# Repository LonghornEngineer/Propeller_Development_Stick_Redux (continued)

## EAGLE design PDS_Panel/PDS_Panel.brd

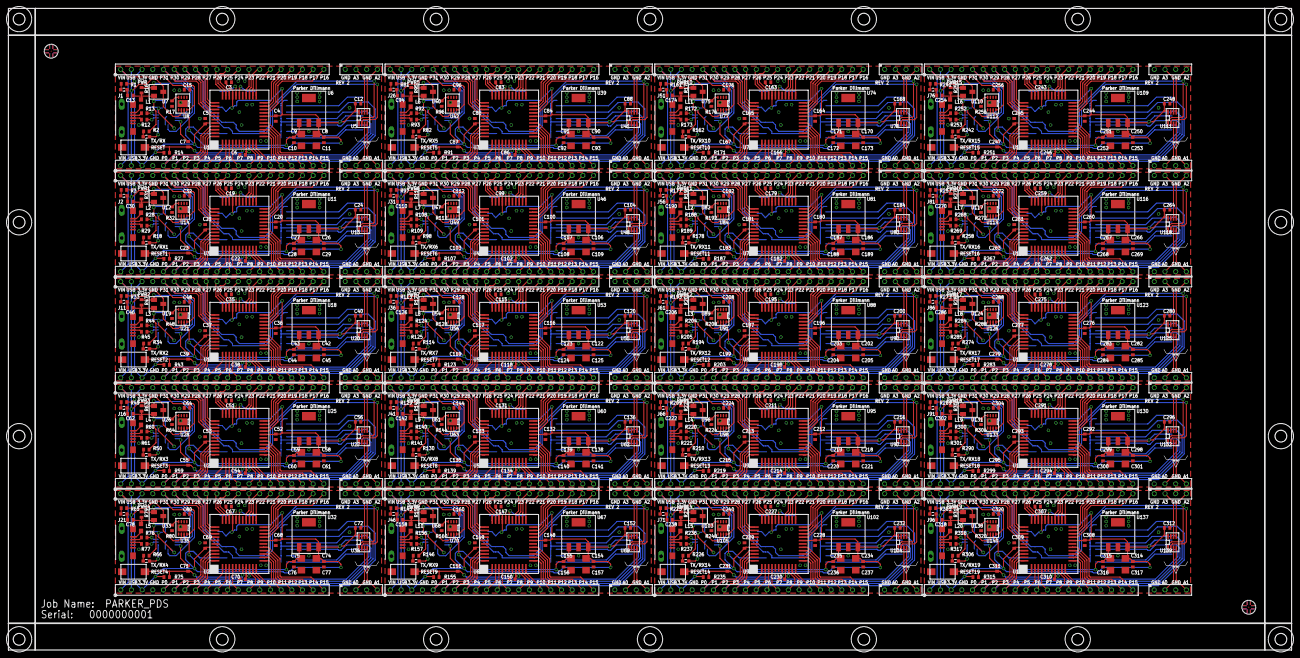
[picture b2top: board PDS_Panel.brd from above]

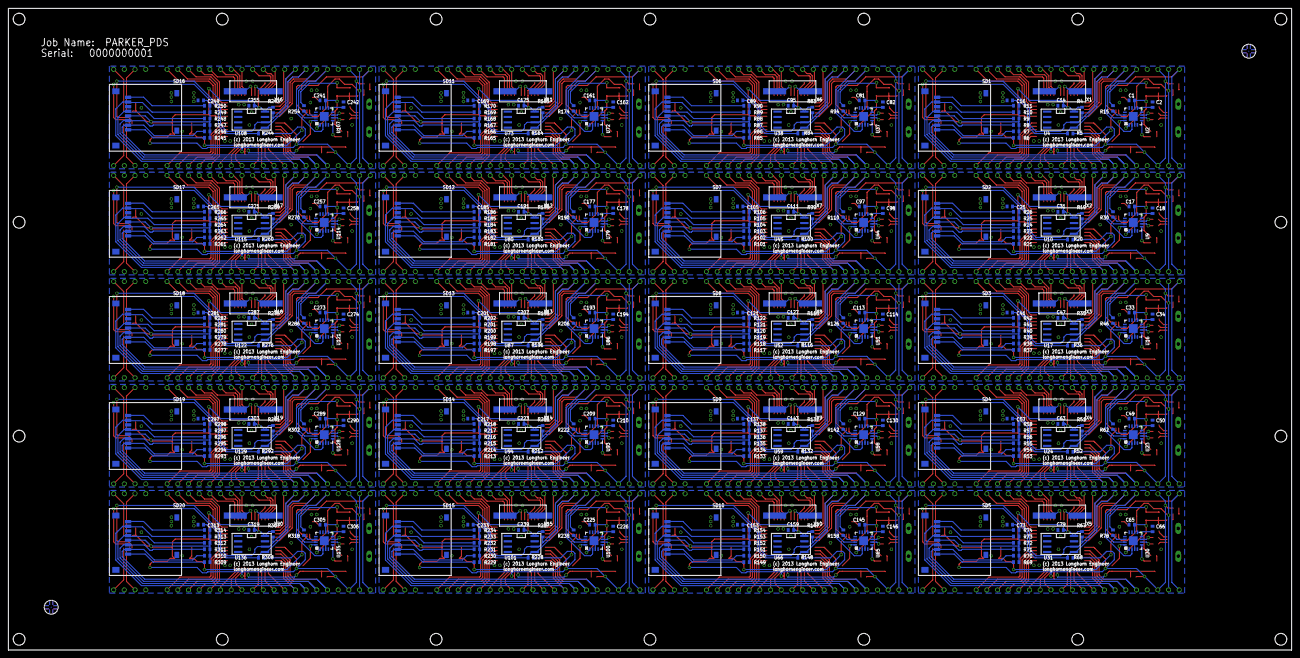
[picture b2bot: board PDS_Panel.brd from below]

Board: 2 copper layers, 304.8 x 152.4 mm, 1062 parts (362 on the bottom side), 1200 nets.

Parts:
C1, C2, C3, C4, C5, C6, C7, C10, C11, C12, C13, C14, C15, C16, C17, C18, C19, C20, C21, C22, C23, C24, C25, C28, C29, C30, C31, C32, C33, C34, C35, C36, C37, C38, C39, C40, C41, C44, C45, C46, C47, C48, C49, C50, C51, C52, C53, C54, C55, C56, C57, C60, C61, C62, C63, C64, C65, C66, C67, C68, C69, C70, C71, C72, C73, C76, C77, C78, C79, C80, C81, C82, C83, C84, C85, C86, C87, C88, C89, C92, C93, C94, C95, C96, C97, C98, C99, C100, C101, C102, C103, C104, C105, C108, C109, C110, C111, C112, C113, C114, C115, C116, C117, C118, C119, C120, C121, C124, C125, C126, C127, C128, C129, C130, C131, C132, C133, C134, C135, C136, C137, C140, C141, C142, C143, C144, C145, C146, C147, C148, C149, C150, C151, C152, C153, C156, C157, C158, C159, C160, C161, C162, C163, C164, C165, C166, C167, C168, C169, C172, C173, C174, C175, C176, C177, C178, C179, C180, C181, C182, C183, C184, C185, C188, C189, C190, C191, C192, C193, C194, C195, C196, C197, C198, C199, C200, C201, C204, C205, C206, C207, C208, C209, C210, C211, C212, C213, C214, C215, C216, C217, C220, C221, C222, C223, C224, C225, C226, C227, C228, C229, C230, C231, C232, C233, C236, C237, C238, C239, C240, C241, C242, C243, C244, C245, C246, C247, C248, C249, C252, C253, C254, C255, C256, C257, C258, C259, C260, C261, C262, C263, C264, C265, C268, C269, C270, C271, C272, C273, C274, C275, C276, C277, C278, C279, C280, C281, C284, C285, C286, C287, C288, C289, C290, C291, C292, C293, C294, C295, C296, C297, C300, C301, C302, C303, C304, C305, C306, C307, C308, C309, C310, C311, C312, C313, C316, C317, C318, C319, C320: .1uF; 0402
C8, C9, C26, C27, C42, C43, C58, C59, C74, C75, C90, C91, C106, C107, C122, C123, C138, C139, C154, C155, C170, C171, C186, C187, C202, C203, C218, C219, C234, C235, C250, C251, C266, C267, C282, C283, C298, C299, C314, C315: 10uF; 1206
E$1, E$2, E$3, E$4, E$5, E$6, E$7, E$8, E$9, E$10, E$11, E$12, E$13, E$14, E$15, E$16, E$17, E$18: MOUNT_HOLE_2.8MM
E$19, E$20, E$21, E$22: FIDUCIAL_PANEL
J1, J2, J11, J16, J21, J26, J31, J36, J41, J46, J51, J56, J61, J66, J71, J76, J81, J86, J91, J96: 10118193-0001LF
J3, J4, J7, J8, J12, J13, J17, J18, J22, J23, J27, J28, J32, J33, J37, J38, J42, J43, J47, J48, J52, J53, J57, J58, J62, J63, J67, J68, J72, J73, J77, J78, J82, J83, J87, J88, J92, J93, J97, J98: M20-7822046; HEADER_01X20_PTH_ROUND
J5, J6, J9, J10, J14, J15, J19, J20, J24, J25, J29, J30, J34, J35, J39, J40, J44, J45, J49, J50, J54, J55, J59, J60, J64, J65, J69, J70, J74, J75, J79, J80, J84, J85, J89, J90, J94, J95, J99, J100: M20-7820442; HEADER_01X04_PTH_ROUND
L1, L2, L3, L4, L5, L6, L7, L8, L9, L10, L11, L12, L13, L14, L15, L16, L17, L18, L19, L20: MI0603K300R-10; 0603
PWR, PWR1, PWR2, PWR3, PWR4, PWR5, PWR6, PWR7, PWR8, PWR9, PWR10, PWR11, PWR12, PWR13, PWR14, PWR15, PWR16, PWR17, PWR18, PWR19: 598-8070-107F; SML0603
R1, R2, R3, R18, R33, R34, R49, R50, R65, R66, R81, R82, R97, R98, R113, R114, R129, R130, R145, R146, R161, R162, R177, R178, R193, R194, R209, R210, R225, R226, R241, R242, R257, R258, R273, R274, R289, R290, R305, R306: 330; 0402
R4, R5, R6, R7, R8, R9, R10, R11, R14, R19, R20, R21, R22, R23, R24, R25, R26, R27, R35, R36, R37, R38, R39, R40, R41, R42, R43, R51, R52, R53, R54, R55, R56, R57, R58, R59, R67, R68, R69, R70, R71, R72, R73, R74, R75, R83, R84, R85, R86, R87, R88, R89, R90, R91, R99, R100, R101, R102, R103, R104, R105, R106, R107, R115, R116, R117, R118, R119, R120, R121, R122, R123, R131, R132, R133, R134, R135, R136, R137, R138, R139, R147, R148, R149, R150, R151, R152, R153, R154, R155, R163, R164, R165, R166, R167, R168, R169, R170, R171, R179, R180, R181, R182, R183, R184, R185, R186, R187, R195, R196, R197, R198, R199, R200, R201, R202, R203, R211, R212, R213, R214, R215, R216, R217, R218, R219, R227, R228, R229, R230, R231, R232, R233, R234, R235, R243, R244, R245, R246, R247, R248, R249, R250, R251, R259, R260, R261, R262, R263, R264, R265, R266, R267, R275, R276, R277, R278, R279, R280, R281, R282, R283, R291, R292, R293, R294, R295, R296, R297, R298, R299, R307, R308, R309, R310, R311, R312, R313, R314, R315: 10K; 0402
R12, R13, R28, R29, R44, R45, R60, R61, R76, R77, R92, R93, R108, R109, R124, R125, R140, R141, R156, R157, R172, R173, R188, R189, R204, R205, R220, R221, R236, R237, R252, R253, R268, R269, R284, R285, R300, R301, R316, R317: 22; 0402
R15, R17, R30, R32, R46, R48, R62, R64, R78, R80, R94, R96, R110, R112, R126, R128, R142, R144, R158, R160, R174, R176, R190, R192, R206, R208, R222, R224, R238, R240, R254, R256, R270, R272, R286, R288, R302, R304, R318, R320: 1K; 0402
R16, R31, R47, R63, R79, R95, R111, R127, R143, R159, R175, R191, R207, R223, R239, R255, R271, R287, R303, R319: 100K; 0402
RESET, RESET1, RESET2, RESET3, RESET4, RESET5, RESET6, RESET7, RESET8, RESET9, RESET10, RESET11, RESET12, RESET13, RESET14, RESET15, RESET16, RESET17, RESET18, RESET19: 101-0134-EV
SD1, SD2, SD3, SD4, SD5, SD6, SD7, SD8, SD9, SD10, SD11, SD12, SD13, SD14, SD15, SD16, SD17, SD18, SD19, SD20: 502570-0893
TX/RX, TX/RX1, TX/RX2, TX/RX3, TX/RX4, TX/RX5, TX/RX6, TX/RX7, TX/RX8, TX/RX9, TX/RX10, TX/RX11, TX/RX12, TX/RX13, TX/RX14, TX/RX15, TX/RX16, TX/RX17, TX/RX18, TX/RX19: 598-8020-107F; SML0603
U1, U3, U15, U22, U29, U36, U43, U50, U57, U64, U71, U78, U85, U92, U99, U106, U113, U120, U127, U134: P8X32A-Q44; LQFP-44
U2, U9, U16, U23, U30, U37, U44, U51, U58, U65, U72, U79, U86, U93, U100, U107, U114, U121, U128, U135: FT230XQ-R; QFN-16
U4, U10, U17, U24, U31, U38, U45, U52, U59, U66, U73, U80, U87, U94, U101, U108, U115, U122, U129, U136: CAT24C512WI-GT3; SOIC-8_W
U5, U13, U20, U27, U34, U41, U48, U55, U62, U69, U76, U83, U90, U97, U104, U111, U118, U125, U132, U139: AD7999YRJZ-1500RL7; SOT-23-8
U6, U11, U18, U25, U32, U39, U46, U53, U60, U67, U74, U81, U88, U95, U102, U109, U116, U123, U130, U137: TS2937CW33; SOT-223
U7, U12, U19, U26, U33, U40, U47, U54, U61, U68, U75, U82, U89, U96, U103, U110, U117, U124, U131, U138: IRLML6401TRPBF; SOT-23
U8, U14, U21, U28, U35, U42, U49, U56, U63, U70, U77, U84, U91, U98, U105, U112, U119, U126, U133, U140: TPS2115ADRBR; SON-8
U$1, U$3, U$5, U$7, U$9, U$11, U$13, U$15, U$17, U$19, U$21, U$23, U$25, U$27, U$29, U$31, U$33, U$35, U$37, U$39: LHE_FRAME
U$2, U$4, U$6, U$8, U$10, U$12, U$14, U$16, U$18, U$20, U$22, U$24, U$26, U$28, U$30, U$32, U$34, U$36, U$38, U$40: LHE_LOGOLHE_LOGO; LHE_LOGO
X1, X2, X3, X4, X5, X6, X7, X8, X9, X10, X11, X12, X13, X14, X15, X16, X17, X18, X19, X20: ATS060CSM-1; HC-49/US_SM

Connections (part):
3.3V: C3.2, C4.2, C5.2, C6.2, C8.1, C11.1, C12.2, C14.1, C16.1, J3.3, J4.3, R1.2, R4.2, R5.2, R6.2, R7.2, R8.2, R9.2, R10.2, R11.2, R14.2, SD1.5, U1.8, U1.18, U1.30, U1.40, U4.8, U5.8, U6.OUT
3.3V1: C19.2, C20.2, C21.2, C22.2, C24.2, C25.1, C26.1, C29.1, C31.1, J7.3, J8.3, R3.2, R19.2, R20.2, R21.2, R22.2, R23.2, R24.2, R25.2, R26.2, R27.2, SD2.5, U3.8, U3.18, U3.30, U3.40, U10.8, U11.OUT, U13.8
3.3V2: C35.2, C36.2, C37.2, C38.2, C40.2, C41.1, C42.1, C45.1, C47.1, J12.3, J13.3, R33.2, R35.2, R36.2, R37.2, R38.2, R39.2, R40.2, R41.2, R42.2, R43.2, SD3.5, U15.8, U15.18, U15.30, U15.40, U17.8, U18.OUT, U20.8
3.3V3: C51.2, C52.2, C53.2, C54.2, C56.2, C57.1, C58.1, C61.1, C63.1, J17.3, J18.3, R49.2, R51.2, R52.2, R53.2, R54.2, R55.2, R56.2, R57.2, R58.2, R59.2, SD4.5, U22.8, U22.18, U22.30, U22.40, U24.8, U25.OUT, U27.8
3.3V4: C67.2, C68.2, C69.2, C70.2, C72.2, C73.1, C74.1, C77.1, C79.1, J22.3, J23.3, R65.2, R67.2, R68.2, R69.2, R70.2, R71.2, R72.2, R73.2, R74.2, R75.2, SD5.5, U29.8, U29.18, U29.30, U29.40, U31.8, U32.OUT, U34.8
3.3V5: C83.2, C84.2, C85.2, C86.2, C88.2, C89.1, C90.1, C93.1, C95.1, J27.3, J28.3, R81.2, R83.2, R84.2, R85.2, R86.2, R87.2, R88.2, R89.2, R90.2, R91.2, SD6.5, U36.8, U36.18, U36.30, U36.40, U38.8, U39.OUT, U41.8
3.3V6: C99.2, C100.2, C101.2, C102.2, C104.2, C105.1, C106.1, C109.1, C111.1, J32.3, J33.3, R97.2, R99.2, R100.2, R101.2, R102.2, R103.2, R104.2, R105.2, R106.2, R107.2, SD7.5, U43.8, U43.18, U43.30, U43.40, U45.8, U46.OUT, U48.8
3.3V7: C115.2, C116.2, C117.2, C118.2, C120.2, C121.1, C122.1, C125.1, C127.1, J37.3, J38.3, R113.2, R115.2, R116.2, R117.2, R118.2, R119.2, R120.2, R121.2, R122.2, R123.2, SD8.5, U50.8, U50.18, U50.30, U50.40, U52.8, U53.OUT, U55.8
3.3V8: C131.2, C132.2, C133.2, C134.2, C136.2, C137.1, C138.1, C141.1, C143.1, J42.3, J43.3, R129.2, R131.2, R132.2, R133.2, R134.2, R135.2, R136.2, R137.2, R138.2, R139.2, SD9.5, U57.8, U57.18, U57.30, U57.40, U59.8, U60.OUT, U62.8
3.3V9: C147.2, C148.2, C149.2, C150.2, C152.2, C153.1, C154.1, C157.1, C159.1, J47.3, J48.3, R145.2, R147.2, R148.2, R149.2, R150.2, R151.2, R152.2, R153.2, R154.2, R155.2, SD10.5, U64.8, U64.18, U64.30, U64.40, U66.8, U67.OUT, U69.8
3.3V10: C163.2, C164.2, C165.2, C166.2, C168.2, C169.1, C170.1, C173.1, C175.1, J52.3, J53.3, R161.2, R163.2, R164.2, R165.2, R166.2, R167.2, R168.2, R169.2, R170.2, R171.2, SD11.5, U71.8, U71.18, U71.30, U71.40, U73.8, U74.OUT, U76.8
3.3V11: C179.2, C180.2, C181.2, C182.2, C184.2, C185.1, C186.1, C189.1, C191.1, J57.3, J58.3, R177.2, R179.2, R180.2, R181.2, R182.2, R183.2, R184.2, R185.2, R186.2, R187.2, SD12.5, U78.8, U78.18, U78.30, U78.40, U80.8, U81.OUT, U83.8
3.3V12: C195.2, C196.2, C197.2, C198.2, C200.2, C201.1, C202.1, C205.1, C207.1, J62.3, J63.3, R193.2, R195.2, R196.2, R197.2, R198.2, R199.2, R200.2, R201.2, R202.2, R203.2, SD13.5, U85.8, U85.18, U85.30, U85.40, U87.8, U88.OUT, U90.8
3.3V13: C211.2, C212.2, C213.2, C214.2, C216.2, C217.1, C218.1, C221.1, C223.1, J67.3, J68.3, R209.2, R211.2, R212.2, R213.2, R214.2, R215.2, R216.2, R217.2, R218.2, R219.2, SD14.5, U92.8, U92.18, U92.30, U92.40, U94.8, U95.OUT, U97.8
3.3V14: C227.2, C228.2, C229.2, C230.2, C232.2, C233.1, C234.1, C237.1, C239.1, J72.3, J73.3, R225.2, R227.2, R228.2, R229.2, R230.2, R231.2, R232.2, R233.2, R234.2, R235.2, SD15.5, U99.8, U99.18, U99.30, U99.40, U101.8, U102.OUT, U104.8
3.3V15: C243.2, C244.2, C245.2, C246.2, C248.2, C249.1, C250.1, C253.1, C255.1, J77.3, J78.3, R241.2, R243.2, R244.2, R245.2, R246.2, R247.2, R248.2, R249.2, R250.2, R251.2, SD16.5, U106.8, U106.18, U106.30, U106.40, U108.8, U109.OUT, U111.8
3.3V16: C259.2, C260.2, C261.2, C262.2, C264.2, C265.1, C266.1, C269.1, C271.1, J82.3, J83.3, R257.2, R259.2, R260.2, R261.2, R262.2, R263.2, R264.2, R265.2, R266.2, R267.2, SD17.5, U113.8, U113.18, U113.30, U113.40, U115.8, U116.OUT, U118.8
3.3V17: C275.2, C276.2, C277.2, C278.2, C280.2, C281.1, C282.1, C285.1, C287.1, J87.3, J88.3, R273.2, R275.2, R276.2, R277.2, R278.2, R279.2, R280.2, R281.2, R282.2, R283.2, SD18.5, U120.8, U120.18, U120.30, U120.40, U122.8, U123.OUT, U125.8
3.3V18: C291.2, C292.2, C293.2, C294.2, C296.2, C297.1, C298.1, C301.1, C303.1, J92.3, J93.3, R289.2, R291.2, R292.2, R293.2, R294.2, R295.2, R296.2, R297.2, R298.2, R299.2, SD19.5, U127.8, U127.18, U127.30, U127.40, U129.8, U130.OUT, U132.8
3.3V19: C307.2, C308.2, C309.2, C310.2, C312.2, C313.1, C314.1, C317.1, C319.1, J97.3, J98.3, R305.2, R307.2, R308.2, R309.2, R310.2, R311.2, R312.2, R313.2, R314.2, R315.2, SD20.5, U134.8, U134.18, U134.30, U134.40, U136.8, U137.OUT, U139.8
3V3OUT: C2.1, U2.1, U2.8, U2.9
3V3OUT1: C18.1, U9.1, U9.8, U9.9
3V3OUT2: C34.1, U16.1, U16.8, U16.9
3V3OUT3: C50.1, U23.1, U23.8, U23.9
3V3OUT4: C66.1, U30.1, U30.8, U30.9
3V3OUT5: C82.1, U37.1, U37.8, U37.9
3V3OUT6: C98.1, U44.1, U44.8, U44.9
3V3OUT7: C114.1, U51.1, U51.8, U51.9
3V3OUT8: C130.1, U58.1, U58.8, U58.9
3V3OUT9: C146.1, U65.1, U65.8, U65.9
3V3OUT10: C162.1, U72.1, U72.8, U72.9
3V3OUT11: C178.1, U79.1, U79.8, U79.9
3V3OUT12: C194.1, U86.1, U86.8, U86.9
3V3OUT13: C210.1, U93.1, U93.8, U93.9
3V3OUT14: C226.1, U100.1, U100.8, U100.9
3V3OUT15: C242.1, U107.1, U107.8, U107.9
3V3OUT16: C258.1, U114.1, U114.8, U114.9
3V3OUT17: C274.1, U121.1, U121.8, U121.9
3V3OUT18: C290.1, U128.1, U128.8, U128.9
3V3OUT19: C306.1, U135.1, U135.8, U135.9
5V: C9.1, C10.1, U6.IN, U8.7
5V1: C27.1, C28.1, U11.IN, U14.7
5V2: C43.1, C44.1, U18.IN, U21.7
5V3: C59.1, C60.1, U25.IN, U28.7
5V4: C75.1, C76.1, U32.IN, U35.7
5V5: C91.1, C92.1, U39.IN, U42.7
5V6: C107.1, C108.1, U46.IN, U49.7
5V7: C123.1, C124.1, U53.IN, U56.7
5V8: C139.1, C140.1, U60.IN, U63.7
5V9: C155.1, C156.1, U67.IN, U70.7
5V10: C171.1, C172.1, U74.IN, U77.7
5V11: C187.1, C188.1, U81.IN, U84.7
5V12: C203.1, C204.1, U88.IN, U91.7
5V13: C219.1, C220.1, U95.IN, U98.7
5V14: C235.1, C236.1, U102.IN, U105.7
5V15: C251.1, C252.1, U109.IN, U112.7
5V16: C267.1, C268.1, U116.IN, U119.7
5V17: C283.1, C284.1, U123.IN, U126.7
5V18: C299.1, C300.1, U130.IN, U133.7
5V19: C315.1, C316.1, U137.IN, U140.7
A0: J6.2, U5.3
A1: J6.4, U5.4
A2: J5.4, U5.5
A3: J5.2, U5.6
A4: J10.2, U13.3
A5: J10.4, U13.4
A6: J9.2, U13.6
A7: J9.4, U13.5
A8: J15.2, U20.3
A9: J15.4, U20.4
A10: J14.2, U20.6
A11: J14.4, U20.5
A12: J20.2, U27.3
A13: J20.4, U27.4
A14: J19.2, U27.6
A15: J19.4, U27.5
A16: J25.2, U34.3
A17: J25.4, U34.4
A18: J24.2, U34.6
A19: J24.4, U34.5
A20: J30.2, U41.3
A21: J30.4, U41.4
A22: J29.2, U41.6
A23: J29.4, U41.5
A24: J35.2, U48.3
A25: J35.4, U48.4
A26: J34.2, U48.6
A27: J34.4, U48.5
A28: J40.2, U55.3
A29: J40.4, U55.4
A30: J39.2, U55.6
A31: J39.4, U55.5
A32: J45.2, U62.3
A33: J45.4, U62.4
A34: J44.2, U62.6
A35: J44.4, U62.5
A36: J50.2, U69.3
A37: J50.4, U69.4
A38: J49.2, U69.6
A39: J49.4, U69.5
A40: J55.2, U76.3
A41: J55.4, U76.4
A42: J54.2, U76.6
A43: J54.4, U76.5
A44: J60.2, U83.3
A45: J60.4, U83.4
A46: J59.2, U83.6
A47: J59.4, U83.5
A48: J65.2, U90.3
A49: J65.4, U90.4
A50: J64.2, U90.6
A51: J64.4, U90.5
A52: J70.2, U97.3
A53: J70.4, U97.4
A54: J69.2, U97.6
A55: J69.4, U97.5
A56: J75.2, U104.3
A57: J75.4, U104.4
A58: J74.2, U104.6
A59: J74.4, U104.5
A60: J80.2, U111.3
A61: J80.4, U111.4
A62: J79.2, U111.6
A63: J79.4, U111.5
A64: J85.2, U118.3
A65: J85.4, U118.4
A66: J84.2, U118.6
A67: J84.4, U118.5
A68: J90.2, U125.3
A69: J90.4, U125.4
A70: J89.2, U125.6
A71: J89.4, U125.5
A72: J95.2, U132.3
A73: J95.4, U132.4
A74: J94.2, U132.6
A75: J94.4, U132.5
A76: J100.2, U139.3
A77: J100.4, U139.4
A78: J99.2, U139.6
A79: J99.4, U139.5
D+: J1.3, R12.2
D+1: J2.3, R29.2
D+2: J11.3, R45.2
D+3: J16.3, R61.2
D+4: J21.3, R77.2
D+5: J26.3, R93.2
D+6: J31.3, R109.2
D+7: J36.3, R125.2
D+8: J41.3, R141.2
D+9: J46.3, R157.2
D+10: J51.3, R173.2
D+11: J56.3, R189.2
D+12: J61.3, R205.2
D+13: J66.3, R221.2
D+14: J71.3, R237.2
D+15: J76.3, R253.2
D+16: J81.3, R269.2
D+17: J86.3, R285.2
D+18: J91.3, R301.2
D+19: J96.3, R317.2
D-: J1.2, R13.2
D-1: J2.2, R28.2
D-2: J11.2, R44.2
D-3: J16.2, R60.2
D-4: J21.2, R76.2
D-5: J26.2, R92.2
D-6: J31.2, R108.2
D-7: J36.2, R124.2
D-8: J41.2, R140.2
D-9: J46.2, R156.2
D-10: J51.2, R172.2
D-11: J56.2, R188.2
D-12: J61.2, R204.2
D-13: J66.2, R220.2
D-14: J71.2, R236.2
D-15: J76.2, R252.2
D-16: J81.2, R268.2
D-17: J86.2, R284.2
D-18: J91.2, R300.2
D-19: J96.2, R316.2
GND: C1.2, C2.2, C3.1, C4.1, C5.1, C6.1, C8.2, C9.2, C10.2, C11.2, C12.1, C13.2, C14.2, C15.1, C16.2, J1.5, J1.S1, J1.S2, J1.S3, J1.S4, J3.4, J4.4, J5.1, J5.3, J6.1, J6.3, PWR.C, R17.2, RESET.1, SD1.3, SD1.SHIELD0, SD1.SHIELD1, SD1.SHIELD2, SD1.SHIELD3, U1.5, U1.6, U1.17, U1.27, U1.39, U2.3, U2.13, U2.PAD, U4.2, U4.3, U4.4, U4.7, U5.7, U6.COM1, U6.COM2, U8.3, U8.5, U8.PAD
GND1: C17.2, C18.2, C19.1, C20.1, C21.1, C22.1, C24.1, C25.2, C26.2, C27.2, C28.2, C29.2, C30.2, C31.2, C32.1, J2.5, J2.S1, J2.S2, J2.S3, J2.S4, J7.4, J8.4, J9.1, J9.3, J10.1, J10.3, PWR1.C, R32.2, RESET1.1, SD2.3, SD2.SHIELD0, SD2.SHIELD1, SD2.SHIELD2, SD2.SHIELD3, U3.5, U3.6, U3.17, U3.27, U3.39, U9.3, U9.13, U9.PAD, U10.2, U10.3, U10.4, U10.7, U11.COM1, U11.COM2, U13.7, U14.3, U14.5, U14.PAD
GND2: C33.2, C34.2, C35.1, C36.1, C37.1, C38.1, C40.1, C41.2, C42.2, C43.2, C44.2, C45.2, C46.2, C47.2, C48.1, J11.5, J11.S1, J11.S2, J11.S3, J11.S4, J12.4, J13.4, J14.1, J14.3, J15.1, J15.3, PWR2.C, R48.2, RESET2.1, SD3.3, SD3.SHIELD0, SD3.SHIELD1, SD3.SHIELD2, SD3.SHIELD3, U15.5, U15.6, U15.17, U15.27, U15.39, U16.3, U16.13, U16.PAD, U17.2, U17.3, U17.4, U17.7, U18.COM1, U18.COM2, U20.7, U21.3, U21.5, U21.PAD
GND3: C49.2, C50.2, C51.1, C52.1, C53.1, C54.1, C56.1, C57.2, C58.2, C59.2, C60.2, C61.2, C62.2, C63.2, C64.1, J16.5, J16.S1, J16.S2, J16.S3, J16.S4, J17.4, J18.4, J19.1, J19.3, J20.1, J20.3, PWR3.C, R64.2, RESET3.1, SD4.3, SD4.SHIELD0, SD4.SHIELD1, SD4.SHIELD2, SD4.SHIELD3, U22.5, U22.6, U22.17, U22.27, U22.39, U23.3, U23.13, U23.PAD, U24.2, U24.3, U24.4, U24.7, U25.COM1, U25.COM2, U27.7, U28.3, U28.5, U28.PAD
GND4: C65.2, C66.2, C67.1, C68.1, C69.1, C70.1, C72.1, C73.2, C74.2, C75.2, C76.2, C77.2, C78.2, C79.2, C80.1, J21.5, J21.S1, J21.S2, J21.S3, J21.S4, J22.4, J23.4, J24.1, J24.3, J25.1, J25.3, PWR4.C, R80.2, RESET4.1, SD5.3, SD5.SHIELD0, SD5.SHIELD1, SD5.SHIELD2, SD5.SHIELD3, U29.5, U29.6, U29.17, U29.27, U29.39, U30.3, U30.13, U30.PAD, U31.2, U31.3, U31.4, U31.7, U32.COM1, U32.COM2, U34.7, U35.3, U35.5, U35.PAD
GND5: C81.2, C82.2, C83.1, C84.1, C85.1, C86.1, C88.1, C89.2, C90.2, C91.2, C92.2, C93.2, C94.2, C95.2, C96.1, J26.5, J26.S1, J26.S2, J26.S3, J26.S4, J27.4, J28.4, J29.1, J29.3, J30.1, J30.3, PWR5.C, R96.2, RESET5.1, SD6.3, SD6.SHIELD0, SD6.SHIELD1, SD6.SHIELD2, SD6.SHIELD3, U36.5, U36.6, U36.17, U36.27, U36.39, U37.3, U37.13, U37.PAD, U38.2, U38.3, U38.4, U38.7, U39.COM1, U39.COM2, U41.7, U42.3, U42.5, U42.PAD
GND6: C97.2, C98.2, C99.1, C100.1, C101.1, C102.1, C104.1, C105.2, C106.2, C107.2, C108.2, C109.2, C110.2, C111.2, C112.1, J31.5, J31.S1, J31.S2, J31.S3, J31.S4, J32.4, J33.4, J34.1, J34.3, J35.1, J35.3, PWR6.C, R112.2, RESET6.1, SD7.3, SD7.SHIELD0, SD7.SHIELD1, SD7.SHIELD2, SD7.SHIELD3, U43.5, U43.6, U43.17, U43.27, U43.39, U44.3, U44.13, U44.PAD, U45.2, U45.3, U45.4, U45.7, U46.COM1, U46.COM2, U48.7, U49.3, U49.5, U49.PAD
GND7: C113.2, C114.2, C115.1, C116.1, C117.1, C118.1, C120.1, C121.2, C122.2, C123.2, C124.2, C125.2, C126.2, C127.2, C128.1, J36.5, J36.S1, J36.S2, J36.S3, J36.S4, J37.4, J38.4, J39.1, J39.3, J40.1, J40.3, PWR7.C, R128.2, RESET7.1, SD8.3, SD8.SHIELD0, SD8.SHIELD1, SD8.SHIELD2, SD8.SHIELD3, U50.5, U50.6, U50.17, U50.27, U50.39, U51.3, U51.13, U51.PAD, U52.2, U52.3, U52.4, U52.7, U53.COM1, U53.COM2, U55.7, U56.3, U56.5, U56.PAD
GND8: C129.2, C130.2, C131.1, C132.1, C133.1, C134.1, C136.1, C137.2, C138.2, C139.2, C140.2, C141.2, C142.2, C143.2, C144.1, J41.5, J41.S1, J41.S2, J41.S3, J41.S4, J42.4, J43.4, J44.1, J44.3, J45.1, J45.3, PWR8.C, R144.2, RESET8.1, SD9.3, SD9.SHIELD0, SD9.SHIELD1, SD9.SHIELD2, SD9.SHIELD3, U57.5, U57.6, U57.17, U57.27, U57.39, U58.3, U58.13, U58.PAD, U59.2, U59.3, U59.4, U59.7, U60.COM1, U60.COM2, U62.7, U63.3, U63.5, U63.PAD
GND9: C145.2, C146.2, C147.1, C148.1, C149.1, C150.1, C152.1, C153.2, C154.2, C155.2, C156.2, C157.2, C158.2, C159.2, C160.1, J46.5, J46.S1, J46.S2, J46.S3, J46.S4, J47.4, J48.4, J49.1, J49.3, J50.1, J50.3, PWR9.C, R160.2, RESET9.1, SD10.3, SD10.SHIELD0, SD10.SHIELD1, SD10.SHIELD2, SD10.SHIELD3, U64.5, U64.6, U64.17, U64.27, U64.39, U65.3, U65.13, U65.PAD, U66.2, U66.3, U66.4, U66.7, U67.COM1, U67.COM2, U69.7, U70.3, U70.5, U70.PAD
GND10: C161.2, C162.2, C163.1, C164.1, C165.1, C166.1, C168.1, C169.2, C170.2, C171.2, C172.2, C173.2, C174.2, C175.2, C176.1, J51.5, J51.S1, J51.S2, J51.S3, J51.S4, J52.4, J53.4, J54.1, J54.3, J55.1, J55.3, PWR10.C, R176.2, RESET10.1, SD11.3, SD11.SHIELD0, SD11.SHIELD1, SD11.SHIELD2, SD11.SHIELD3, U71.5, U71.6, U71.17, U71.27, U71.39, U72.3, U72.13, U72.PAD, U73.2, U73.3, U73.4, U73.7, U74.COM1, U74.COM2, U76.7, U77.3, U77.5, U77.PAD
GND11: C177.2, C178.2, C179.1, C180.1, C181.1, C182.1, C184.1, C185.2, C186.2, C187.2, C188.2, C189.2, C190.2, C191.2, C192.1, J56.5, J56.S1, J56.S2, J56.S3, J56.S4, J57.4, J58.4, J59.1, J59.3, J60.1, J60.3, PWR11.C, R192.2, RESET11.1, SD12.3, SD12.SHIELD0, SD12.SHIELD1, SD12.SHIELD2, SD12.SHIELD3, U78.5, U78.6, U78.17, U78.27, U78.39, U79.3, U79.13, U79.PAD, U80.2, U80.3, U80.4, U80.7, U81.COM1, U81.COM2, U83.7, U84.3, U84.5, U84.PAD
GND12: C193.2, C194.2, C195.1, C196.1, C197.1, C198.1, C200.1, C201.2, C202.2, C203.2, C204.2, C205.2, C206.2, C207.2, C208.1, J61.5, J61.S1, J61.S2, J61.S3, J61.S4, J62.4, J63.4, J64.1, J64.3, J65.1, J65.3, PWR12.C, R208.2, RESET12.1, SD13.3, SD13.SHIELD0, SD13.SHIELD1, SD13.SHIELD2, SD13.SHIELD3, U85.5, U85.6, U85.17, U85.27, U85.39, U86.3, U86.13, U86.PAD, U87.2, U87.3, U87.4, U87.7, U88.COM1, U88.COM2, U90.7, U91.3, U91.5, U91.PAD
GND13: C209.2, C210.2, C211.1, C212.1, C213.1, C214.1, C216.1, C217.2, C218.2, C219.2, C220.2, C221.2, C222.2, C223.2, C224.1, J66.5, J66.S1, J66.S2, J66.S3, J66.S4, J67.4, J68.4, J69.1, J69.3, J70.1, J70.3, PWR13.C, R224.2, RESET13.1, SD14.3, SD14.SHIELD0, SD14.SHIELD1, SD14.SHIELD2, SD14.SHIELD3, U92.5, U92.6, U92.17, U92.27, U92.39, U93.3, U93.13, U93.PAD, U94.2, U94.3, U94.4, U94.7, U95.COM1, U95.COM2, U97.7, U98.3, U98.5, U98.PAD
GND14: C225.2, C226.2, C227.1, C228.1, C229.1, C230.1, C232.1, C233.2, C234.2, C235.2, C236.2, C237.2, C238.2, C239.2, C240.1, J71.5, J71.S1, J71.S2, J71.S3, J71.S4, J72.4, J73.4, J74.1, J74.3, J75.1, J75.3, PWR14.C, R240.2, RESET14.1, SD15.3, SD15.SHIELD0, SD15.SHIELD1, SD15.SHIELD2, SD15.SHIELD3, U99.5, U99.6, U99.17, U99.27, U99.39, U100.3, U100.13, U100.PAD, U101.2, U101.3, U101.4, U101.7, U102.COM1, U102.COM2, U104.7, U105.3, U105.5, U105.PAD
GND15: C241.2, C242.2, C243.1, C244.1, C245.1, C246.1, C248.1, C249.2, C250.2, C251.2, C252.2, C253.2, C254.2, C255.2, C256.1, J76.5, J76.S1, J76.S2, J76.S3, J76.S4, J77.4, J78.4, J79.1, J79.3, J80.1, J80.3, PWR15.C, R256.2, RESET15.1, SD16.3, SD16.SHIELD0, SD16.SHIELD1, SD16.SHIELD2, SD16.SHIELD3, U106.5, U106.6, U106.17, U106.27, U106.39, U107.3, U107.13, U107.PAD, U108.2, U108.3, U108.4, U108.7, U109.COM1, U109.COM2, U111.7, U112.3, U112.5, U112.PAD
GND16: C257.2, C258.2, C259.1, C260.1, C261.1, C262.1, C264.1, C265.2, C266.2, C267.2, C268.2, C269.2, C270.2, C271.2, C272.1, J81.5, J81.S1, J81.S2, J81.S3, J81.S4, J82.4, J83.4, J84.1, J84.3, J85.1, J85.3, PWR16.C, R272.2, RESET16.1, SD17.3, SD17.SHIELD0, SD17.SHIELD1, SD17.SHIELD2, SD17.SHIELD3, U113.5, U113.6, U113.17, U113.27, U113.39, U114.3, U114.13, U114.PAD, U115.2, U115.3, U115.4, U115.7, U116.COM1, U116.COM2, U118.7, U119.3, U119.5, U119.PAD
GND17: C273.2, C274.2, C275.1, C276.1, C277.1, C278.1, C280.1, C281.2, C282.2, C283.2, C284.2, C285.2, C286.2, C287.2, C288.1, J86.5, J86.S1, J86.S2, J86.S3, J86.S4, J87.4, J88.4, J89.1, J89.3, J90.1, J90.3, PWR17.C, R288.2, RESET17.1, SD18.3, SD18.SHIELD0, SD18.SHIELD1, SD18.SHIELD2, SD18.SHIELD3, U120.5, U120.6, U120.17, U120.27, U120.39, U121.3, U121.13, U121.PAD, U122.2, U122.3, U122.4, U122.7, U123.COM1, U123.COM2, U125.7, U126.3, U126.5, U126.PAD
GND18: C289.2, C290.2, C291.1, C292.1, C293.1, C294.1, C296.1, C297.2, C298.2, C299.2, C300.2, C301.2, C302.2, C303.2, C304.1, J91.5, J91.S1, J91.S2, J91.S3, J91.S4, J92.4, J93.4, J94.1, J94.3, J95.1, J95.3, PWR18.C, R304.2, RESET18.1, SD19.3, SD19.SHIELD0, SD19.SHIELD1, SD19.SHIELD2, SD19.SHIELD3, U127.5, U127.6, U127.17, U127.27, U127.39, U128.3, U128.13, U128.PAD, U129.2, U129.3, U129.4, U129.7, U130.COM1, U130.COM2, U132.7, U133.3, U133.5, U133.PAD
GND19: C305.2, C306.2, C307.1, C308.1, C309.1, C310.1, C312.1, C313.2, C314.2, C315.2, C316.2, C317.2, C318.2, C319.2, C320.1, J96.5, J96.S1, J96.S2, J96.S3, J96.S4, J97.4, J98.4, J99.1, J99.3, J100.1, J100.3, PWR19.C, R320.2, RESET19.1, SD20.3, SD20.SHIELD0, SD20.SHIELD1, SD20.SHIELD2, SD20.SHIELD3, U134.5, U134.6, U134.17, U134.27, U134.39, U135.3, U135.13, U135.PAD, U136.2, U136.3, U136.4, U136.7, U137.COM1, U137.COM2, U139.7, U140.3, U140.5, U140.PAD
IRQ: R11.1, SD1.1
IRQ1: R26.1, SD2.1
IRQ2: R42.1, SD3.1
IRQ3: R58.1, SD4.1
IRQ4: R74.1, SD5.1
IRQ5: R90.1, SD6.1
IRQ6: R106.1, SD7.1
IRQ7: R122.1, SD8.1
IRQ8: R138.1, SD9.1
IRQ9: R154.1, SD10.1
IRQ10: R170.1, SD11.1
IRQ11: R186.1, SD12.1
IRQ12: R202.1, SD13.1
IRQ13: R218.1, SD14.1
IRQ14: R234.1, SD15.1
IRQ15: R250.1, SD16.1
IRQ16: R266.1, SD17.1
IRQ17: R282.1, SD18.1
IRQ18: R298.1, SD19.1
IRQ19: R314.1, SD20.1
unnamed: PWR.A, R1.1
unnamed: R2.1, TX/RX.A
unnamed: R30.1, R31.1, U12.1
unnamed: PWR1.A, R3.1
unnamed: R18.1, TX/RX1.A
unnamed: R32.1, U14.4
unnamed: R17.1, U8.4
unnamed: R46.1, R47.1, U19.1
unnamed: PWR2.A, R33.1
unnamed: R34.1, TX/RX2.A
unnamed: R48.1, U21.4
unnamed: R62.1, R63.1, U26.1
unnamed: PWR3.A, R49.1
unnamed: R50.1, TX/RX3.A
unnamed: R64.1, U28.4
unnamed: R78.1, R79.1, U33.1
unnamed: PWR4.A, R65.1
unnamed: R66.1, TX/RX4.A
unnamed: R80.1, U35.4
unnamed: R94.1, R95.1, U40.1
unnamed: PWR5.A, R81.1
unnamed: R82.1, TX/RX5.A
unnamed: R96.1, U42.4
unnamed: R110.1, R111.1, U47.1
unnamed: PWR6.A, R97.1
unnamed: R98.1, TX/RX6.A
unnamed: R112.1, U49.4
unnamed: R126.1, R127.1, U54.1
unnamed: PWR7.A, R113.1
unnamed: R114.1, TX/RX7.A
unnamed: R128.1, U56.4
unnamed: R142.1, R143.1, U61.1
unnamed: PWR8.A, R129.1
unnamed: R130.1, TX/RX8.A
unnamed: R144.1, U63.4
unnamed: R158.1, R159.1, U68.1
unnamed: PWR9.A, R145.1
unnamed: R146.1, TX/RX9.A
unnamed: R160.1, U70.4
unnamed: R174.1, R175.1, U75.1
unnamed: R15.1, R16.1, U7.1
unnamed: PWR10.A, R161.1
unnamed: R162.1, TX/RX10.A
unnamed: R176.1, U77.4
unnamed: R190.1, R191.1, U82.1
unnamed: PWR11.A, R177.1
unnamed: R178.1, TX/RX11.A
unnamed: R192.1, U84.4
unnamed: R206.1, R207.1, U89.1
unnamed: PWR12.A, R193.1
unnamed: R194.1, TX/RX12.A
unnamed: R208.1, U91.4
unnamed: R222.1, R223.1, U96.1
unnamed: PWR13.A, R209.1
unnamed: R210.1, TX/RX13.A
unnamed: R224.1, U98.4
unnamed: R238.1, R239.1, U103.1
unnamed: PWR14.A, R225.1
unnamed: R226.1, TX/RX14.A
unnamed: R240.1, U105.4
unnamed: R254.1, R255.1, U110.1
unnamed: PWR15.A, R241.1
unnamed: R242.1, TX/RX15.A
unnamed: R256.1, U112.4
unnamed: R270.1, R271.1, U117.1
unnamed: PWR16.A, R257.1
unnamed: R258.1, TX/RX16.A
unnamed: R272.1, U119.4
unnamed: R286.1, R287.1, U124.1
unnamed: PWR17.A, R273.1
unnamed: R274.1, TX/RX17.A
unnamed: R288.1, U126.4
unnamed: R302.1, R303.1, U131.1
unnamed: PWR18.A, R289.1
unnamed: R290.1, TX/RX18.A
unnamed: R304.1, U133.4
unnamed: R318.1, R319.1, U138.1
unnamed: PWR19.A, R305.1
unnamed: R306.1, TX/RX19.A
unnamed: R320.1, U140.4
P1: J8.9, U3.34
P2: J8.10, U3.33
P3: J8.13, U3.26
P4: J3.9, U1.1
P5: J3.10, U1.2
P6: J3.11, U1.3
P7: J3.12, U1.4
P8: J3.13, U1.9
P9: J3.14, U1.10
P10: J3.15, U1.11
P11: J3.16, U1.12
P12: J3.17, U1.13
P13: J3.18, U1.14
P14: J3.19, U1.15
P15: J3.20, U1.16
P16: J4.20, U1.19
P17: J4.19, U1.20
P18: J4.18, U1.21
P19: J4.17, U1.22
P20: J4.16, U1.23
P21: J4.15, U1.24
P22: J4.14, U1.25
P23: J4.13, U1.26
P24: J4.12, U1.31
P25: J4.11, U1.32
P26: J4.10, U1.33
P27: J4.9, U1.34
P28: J8.14, U3.25
P29: J8.15, U3.24
P30: J8.16, U3.23
P31: J8.17, U3.22
P32: J8.18, U3.21
P33: J8.19, U3.20
P34: J8.20, U3.19
P35: J7.9, U3.1
P36: J7.16, U3.12
P37: J7.15, U3.11
P38: J7.14, U3.10
P39: J7.13, U3.9
P40: J7.12, U3.4
P41: J7.11, U3.3
P42: J7.10, U3.2
P43: J8.11, U3.32
P44: J8.12, U3.31
P45: J7.19, U3.15
P46: J7.20, U3.16
P47: J7.18, U3.14
P48: J7.17, U3.13
P49: J13.9, U15.34
P50: J13.10, U15.33
P51: J13.13, U15.26
P52: J13.14, U15.25
P53: J13.15, U15.24
P54: J13.16, U15.23
P55: J13.17, U15.22
P56: J13.18, U15.21
P57: J13.19, U15.20
P58: J13.20, U15.19
P59: J12.9, U15.1
P60: J12.16, U15.12
P61: J12.15, U15.11
P62: J12.14, U15.10
P63: J12.13, U15.9
P64: J12.12, U15.4
P65: J12.11, U15.3
P66: J12.10, U15.2
P67: J13.11, U15.32
P68: J13.12, U15.31
P69: J12.19, U15.15
P70: J12.20, U15.16
P71: J12.18, U15.14
P72: J12.17, U15.13
P73: J18.9, U22.34
P74: J18.10, U22.33
P75: J18.13, U22.26
P76: J18.14, U22.25
P77: J18.15, U22.24
P78: J18.16, U22.23
P79: J18.17, U22.22
P80: J18.18, U22.21
P81: J18.19, U22.20
P82: J18.20, U22.19
P83: J17.9, U22.1
P84: J17.16, U22.12
P85: J17.15, U22.11
P86: J17.14, U22.10
P87: J17.13, U22.9
P88: J17.12, U22.4
P89: J17.11, U22.3
P90: J17.10, U22.2
P91: J18.11, U22.32
P92: J18.12, U22.31
P93: J17.19, U22.15
P94: J17.20, U22.16
P95: J17.18, U22.14
P96: J17.17, U22.13
P97: J23.9, U29.34
P98: J23.10, U29.33
P99: J23.13, U29.26
P100: J23.14, U29.25
P101: J23.15, U29.24
P102: J23.16, U29.23
P103: J23.17, U29.22
P104: J23.18, U29.21
P105: J23.19, U29.20
P106: J23.20, U29.19
P107: J22.9, U29.1
P108: J22.16, U29.12
P109: J22.15, U29.11
P110: J22.14, U29.10
P111: J22.13, U29.9
P112: J22.12, U29.4
P113: J22.11, U29.3
P114: J22.10, U29.2
P115: J23.11, U29.32
P116: J23.12, U29.31
P117: J22.19, U29.15
P118: J22.20, U29.16
P119: J22.18, U29.14
P120: J22.17, U29.13
P121: J28.9, U36.34
P122: J28.10, U36.33
P123: J28.13, U36.26
P124: J28.14, U36.25
P125: J28.15, U36.24
P126: J28.16, U36.23
P127: J28.17, U36.22
P128: J28.18, U36.21
P129: J28.19, U36.20
P130: J28.20, U36.19
P131: J27.9, U36.1
P132: J27.16, U36.12
P133: J27.15, U36.11
P134: J27.14, U36.10
P135: J27.13, U36.9
P136: J27.12, U36.4
P137: J27.11, U36.3
P138: J27.10, U36.2
P139: J28.11, U36.32
P140: J28.12, U36.31
P141: J27.19, U36.15
P142: J27.20, U36.16
P143: J27.18, U36.14
P144: J27.17, U36.13
P145: J33.9, U43.34
P146: J33.10, U43.33
P147: J33.13, U43.26
P148: J33.14, U43.25
P149: J33.15, U43.24
P150: J33.16, U43.23
P151: J33.17, U43.22
P152: J33.18, U43.21
P153: J33.19, U43.20
P154: J33.20, U43.19
P155: J32.9, U43.1
P156: J32.16, U43.12
P157: J32.15, U43.11
P158: J32.14, U43.10
P159: J32.13, U43.9
P160: J32.12, U43.4
P161: J32.11, U43.3
P162: J32.10, U43.2
P163: J33.11, U43.32
P164: J33.12, U43.31
P165: J32.19, U43.15
P166: J32.20, U43.16
P167: J32.18, U43.14
P168: J32.17, U43.13
P169: J38.9, U50.34
P170: J38.10, U50.33
P171: J38.13, U50.26
P172: J38.14, U50.25
P173: J38.15, U50.24
P174: J38.16, U50.23
P175: J38.17, U50.22
P176: J38.18, U50.21
P177: J38.19, U50.20
P178: J38.20, U50.19
P179: J37.9, U50.1
P180: J37.16, U50.12
P181: J37.15, U50.11
P182: J37.14, U50.10
P183: J37.13, U50.9
P184: J37.12, U50.4
P185: J37.11, U50.3
P186: J37.10, U50.2
P187: J38.11, U50.32
P188: J38.12, U50.31
P189: J37.19, U50.15
P190: J37.20, U50.16
P191: J37.18, U50.14
P192: J37.17, U50.13
P193: J43.9, U57.34
P194: J43.10, U57.33
P195: J43.13, U57.26
P196: J43.14, U57.25
P197: J43.15, U57.24
P198: J43.16, U57.23
P199: J43.17, U57.22
P200: J43.18, U57.21
P201: J43.19, U57.20
P202: J43.20, U57.19
P203: J42.9, U57.1
P204: J42.16, U57.12
P205: J42.15, U57.11
P206: J42.14, U57.10
P207: J42.13, U57.9
P208: J42.12, U57.4
P209: J42.11, U57.3
P210: J42.10, U57.2
P211: J43.11, U57.32
P212: J43.12, U57.31
P213: J42.19, U57.15
P214: J42.20, U57.16
P215: J42.18, U57.14
P216: J42.17, U57.13
P217: J48.9, U64.34
P218: J48.10, U64.33
P219: J48.13, U64.26
P220: J48.14, U64.25
P221: J48.15, U64.24
P222: J48.16, U64.23
P223: J48.17, U64.22
P224: J48.18, U64.21
P225: J48.19, U64.20
P226: J48.20, U64.19
P227: J47.9, U64.1
P228: J47.16, U64.12
P229: J47.15, U64.11
P230: J47.14, U64.10
P231: J47.13, U64.9
P232: J47.12, U64.4
P233: J47.11, U64.3
P234: J47.10, U64.2
P235: J48.11, U64.32
P236: J48.12, U64.31
P237: J47.19, U64.15
P238: J47.20, U64.16
P239: J47.18, U64.14
P240: J47.17, U64.13
P241: J53.9, U71.34
P242: J53.10, U71.33
P243: J53.13, U71.26
P244: J53.14, U71.25
P245: J53.15, U71.24
P246: J53.16, U71.23
P247: J53.17, U71.22
P248: J53.18, U71.21
P249: J53.19, U71.20
P250: J53.20, U71.19
P251: J52.9, U71.1
P252: J52.16, U71.12
P253: J52.15, U71.11
P254: J52.14, U71.10
P255: J52.13, U71.9
P256: J52.12, U71.4
P257: J52.11, U71.3
P258: J52.10, U71.2
P259: J53.11, U71.32
P260: J53.12, U71.31
P261: J52.19, U71.15
P262: J52.20, U71.16
P263: J52.18, U71.14
P264: J52.17, U71.13
P265: J58.9, U78.34
P266: J58.10, U78.33
P267: J58.13, U78.26
P268: J58.14, U78.25
P269: J58.15, U78.24
P270: J58.16, U78.23
P271: J58.17, U78.22
P272: J58.18, U78.21
P273: J58.19, U78.20
P274: J58.20, U78.19
P275: J57.9, U78.1
P276: J57.16, U78.12
P277: J57.15, U78.11
P278: J57.14, U78.10
P279: J57.13, U78.9
P280: J57.12, U78.4
P281: J57.11, U78.3
P282: J57.10, U78.2
P283: J58.11, U78.32
P284: J58.12, U78.31
P285: J57.19, U78.15
P286: J57.20, U78.16
P287: J57.18, U78.14
P288: J57.17, U78.13
P289: J63.9, U85.34
P290: J63.10, U85.33
P291: J63.13, U85.26
P292: J63.14, U85.25
P293: J63.15, U85.24
P294: J63.16, U85.23
P295: J63.17, U85.22
P296: J63.18, U85.21
P297: J63.19, U85.20
P298: J63.20, U85.19
P299: J62.9, U85.1
P300: J62.16, U85.12
P301: J62.15, U85.11
P302: J62.14, U85.10
P303: J62.13, U85.9
P304: J62.12, U85.4
P305: J62.11, U85.3
P306: J62.10, U85.2
P307: J63.11, U85.32
P308: J63.12, U85.31
P309: J62.19, U85.15
P310: J62.20, U85.16
P311: J62.18, U85.14
P312: J62.17, U85.13
P313: J68.9, U92.34
P314: J68.10, U92.33
P315: J68.13, U92.26
P316: J68.14, U92.25
P317: J68.15, U92.24
P318: J68.16, U92.23
P319: J68.17, U92.22
P320: J68.18, U92.21
P321: J68.19, U92.20
P322: J68.20, U92.19
P323: J67.9, U92.1
P324: J67.16, U92.12
P325: J67.15, U92.11
P326: J67.14, U92.10
P327: J67.13, U92.9
P328: J67.12, U92.4
P329: J67.11, U92.3
P330: J67.10, U92.2
P331: J68.11, U92.32
P332: J68.12, U92.31
P333: J67.19, U92.15
P334: J67.20, U92.16
P335: J67.18, U92.14
P336: J67.17, U92.13
P337: J73.9, U99.34
P338: J73.10, U99.33
P339: J73.13, U99.26
P340: J73.14, U99.25
P341: J73.15, U99.24
P342: J73.16, U99.23
P343: J73.17, U99.22
P344: J73.18, U99.21
P345: J73.19, U99.20
P346: J73.20, U99.19
P347: J72.9, U99.1
P348: J72.16, U99.12
P349: J72.15, U99.11
P350: J72.14, U99.10
P351: J72.13, U99.9
P352: J72.12, U99.4
P353: J72.11, U99.3
P354: J72.10, U99.2
P355: J73.11, U99.32
P356: J73.12, U99.31
P357: J72.19, U99.15
P358: J72.20, U99.16
P359: J72.18, U99.14
P360: J72.17, U99.13
P361: J78.9, U106.34
P362: J78.10, U106.33
P363: J78.13, U106.26
P364: J78.14, U106.25
P365: J78.15, U106.24
P366: J78.16, U106.23
P367: J78.17, U106.22
P368: J78.18, U106.21
P369: J78.19, U106.20
P370: J78.20, U106.19
P371: J77.9, U106.1
P372: J77.16, U106.12
P373: J77.15, U106.11
P374: J77.14, U106.10
P375: J77.13, U106.9
P376: J77.12, U106.4
P377: J77.11, U106.3
P378: J77.10, U106.2
P379: J78.11, U106.32
P380: J78.12, U106.31
P381: J77.19, U106.15
P382: J77.20, U106.16
P383: J77.18, U106.14
P384: J77.17, U106.13
P385: J83.9, U113.34
P386: J83.10, U113.33
P387: J83.13, U113.26
P388: J83.14, U113.25
P389: J83.15, U113.24
P390: J83.16, U113.23
P391: J83.17, U113.22
P392: J83.18, U113.21
P393: J83.19, U113.20
P394: J83.20, U113.19
P395: J82.9, U113.1
P396: J82.16, U113.12
P397: J82.15, U113.11
P398: J82.14, U113.10
P399: J82.13, U113.9
P400: J82.12, U113.4
P401: J82.11, U113.3
P402: J82.10, U113.2
P403: J83.11, U113.32
P404: J83.12, U113.31
P405: J82.19, U113.15
P406: J82.20, U113.16
P407: J82.18, U113.14
P408: J82.17, U113.13
P409: J88.9, U120.34
P410: J88.10, U120.33
P411: J88.13, U120.26
P412: J88.14, U120.25
P413: J88.15, U120.24
P414: J88.16, U120.23
P415: J88.17, U120.22
P416: J88.18, U120.21
P417: J88.19, U120.20
P418: J88.20, U120.19
P419: J87.9, U120.1
P420: J87.16, U120.12
P421: J87.15, U120.11
P422: J87.14, U120.10
P423: J87.13, U120.9
P424: J87.12, U120.4
P425: J87.11, U120.3
P426: J87.10, U120.2
P427: J88.11, U120.32
P428: J88.12, U120.31
P429: J87.19, U120.15
P430: J87.20, U120.16
P431: J87.18, U120.14
P432: J87.17, U120.13
P433: J93.9, U127.34
P434: J93.10, U127.33
P435: J93.13, U127.26
P436: J93.14, U127.25
P437: J93.15, U127.24
P438: J93.16, U127.23
P439: J93.17, U127.22
P440: J93.18, U127.21
P441: J93.19, U127.20
P442: J93.20, U127.19
P443: J92.9, U127.1
P444: J92.16, U127.12
P445: J92.15, U127.11
P446: J92.14, U127.10
P447: J92.13, U127.9
P448: J92.12, U127.4
P449: J92.11, U127.3
P450: J92.10, U127.2
P451: J93.11, U127.32
P452: J93.12, U127.31
P453: J92.19, U127.15
P454: J92.20, U127.16
P455: J92.18, U127.14
P456: J92.17, U127.13
P457: J98.9, U134.34
P458: J98.10, U134.33
P459: J98.13, U134.26
P460: J98.14, U134.25
P461: J98.15, U134.24
P462: J98.16, U134.23
P463: J98.17, U134.22
P464: J98.18, U134.21
P465: J98.19, U134.20
P466: J98.20, U134.19
P467: J97.9, U134.1
P468: J97.16, U134.12
P469: J97.15, U134.11
P470: J97.14, U134.10
P471: J97.13, U134.9
P472: J97.12, U134.4
P473: J97.11, U134.3
P474: J97.10, U134.2
P475: J98.11, U134.32
P476: J98.12, U134.31
P477: J97.19, U134.15
P478: J97.20, U134.16
P479: J97.18, U134.14
P480: J97.17, U134.13
PWREN: R15.2, U2.14
PWREN1: R30.2, U9.14
PWREN2: R46.2, U16.14
PWREN3: R62.2, U23.14
PWREN4: R78.2, U30.14
PWREN5: R94.2, U37.14
PWREN6: R110.2, U44.14
PWREN7: R126.2, U51.14
PWREN8: R142.2, U58.14
PWREN9: R158.2, U65.14
PWREN10: R174.2, U72.14
PWREN11: R190.2, U79.14
PWREN12: R206.2, U86.14
PWREN13: R222.2, U93.14
PWREN14: R238.2, U100.14
PWREN15: R254.2, U107.14
PWREN16: R270.2, U114.14
PWREN17: R286.2, U121.14
PWREN18: R302.2, U128.14
PWREN19: R318.2, U135.14
RES: C7.2, R14.1, RESET.2, U1.7
RES1: C23.2, R27.1, RESET1.2, U3.7
RES2: C39.2, R43.1, RESET2.2, U15.7
RES3: C55.2, R59.1, RESET3.2, U22.7
RES4: C71.2, R75.1, RESET4.2, U29.7
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
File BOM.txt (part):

Partlist exported from C:/Users/Parker/Documents/GitHub/Propeller_Development_Stick_Redux/Prop_Dev_Stick.sch at 12/28/2014 2:22:21 PM

Part  Value                    Device                        Package                Description                    DNAME           MFG# PNAME               REVNUM TEMP_COF TOLERANCE VOLTAGE
C1    .1uF                     CAPACITOR_NON_POLAR0603       0603                   Capacitor Non Polarized                                                                                  
C2    .1uF                     CAPACITOR_NON_POLAR0603       0603                   Capacitor Non Polarized                                                                                  
C3    .1uF                     CAPACITOR_NON_POLAR0603       0603                   Capacitor Non Polarized                                                                                  
C4    .1uF                     CAPACITOR_NON_POLAR0603       0603                   Capacitor Non Polarized                                                                                  
C5    .1uF                     CAPACITOR_NON_POLAR0603       0603                   Capacitor Non Polarized                                                                                  
C6    .1uF                     CAPACITOR_NON_POLAR0603       0603                   Capacitor Non Polarized                                                                                  
C7    .1uF                     CAPACITOR_NON_POLAR0603       0603                   Capacitor Non Polarized                                                                                  
C8    10uF                     CAPACITOR_NP_1206             C1206                  Library:  MF_Passives                          N/A                             N/A      N/A       N/A    
C9    10uF                     CAPACITOR_NP_1206             C1206                  Library:  MF_Passives                          N/A                             N/A      N/A       N/A    
C10   .1uF                     CAPACITOR_NON_POLAR0603       0603                   Capacitor Non Polarized                                                                                  
C11   .1uF                     CAPACITOR_NON_POLAR0603       0603                   Capacitor Non Polarized                                                                                  
C12   .1uF                     CAPACITOR_NON_POLAR0603       0603                   Capacitor Non Polarized                                                                                  
C13   1uF                      CAPACITOR_NON_POLAR0603       0603                   Capacitor Non Polarized                                                                                  
C14   .1uF                     CAPACITOR_NON_POLAR0603       0603                   Capacitor Non Polarized                                                                                  
C15   .1uF                     CAPACITOR_NON_POLAR0603       0603                   Capacitor Non Polarized                                                                                  
C16   .1uF                     CAPACITOR_NON_POLAR0603       0603                   Capacitor Non Polarized                                                                                  
C17   10uF                     CAPACITOR_P_4MM               CP4MM                  Library:  MF_Passives                          N/A                                      N/A       N/A    
J1    MF-CON-MICROUSB-RIGHT    USB_CON_5PRIGHT               MICROUSB-RIGHT         Library:  MF_Connectors                                                                                  
J3    M20-7822046              PH_1X20HEADER_01X20_PTH_ROUND HEADER_01X20_PTH_ROUND                                                                                                          
J4    M20-7822046              PH_1X20HEADER_01X20_PTH_ROUND HEADER_01X20_PTH_ROUND                                                                                                          
J5    M20-7820442              PH_1X04HEADER_PTH_ROUND       HEADER_01X04_PTH_ROUND 4 Pin Connectors                                                                                         
J6    M20-7820442              PH_1X04HEADER_PTH_ROUND       HEADER_01X04_PTH_ROUND 4 Pin Connectors                                                                                         
L1    MI0603K300R-10           INDUCTOR0603                  0603                   Inductors                                                                                                
PWR   598-8020-107F            LED_SINGLE0805                LED_0805                                                                                                                        
R1    330                      RESISTOR0603                  0603                   Resistors                                                                                                
R2    330                      RESISTOR0603                  0603                   Resistors                                                                                                
R3    100K                     RESISTOR0603                  0603                   Resistors                                                                                                
R4    10K                      RESISTOR0603                  0603                   Resistors                                                                                                
R5    10K                      RESISTOR0603                  0603                   Resistors                                                                                                
R6    10K                      RESISTOR0603                  0603                   Resistors                                                                                                
R7    10K                      RESISTOR0603                  0603                   Resistors                                                                                                
R8    10K                      RESISTOR0603                  0603                   Resistors                                                                                                
R9    10K                      RESISTOR0603                  0603                   Resistors                                                                                                
R10   10K                      RESISTOR0603                  0603                   Resistors                                                                                                
R11   10K                      RESISTOR0603                  0603                   Resistors                                                                                                
R12   22                       RESISTOR0603                  0603                   Resistors                                                                                                
R13   22                       RESISTOR0603                  0603                   Resistors                                                                                                
R14   10K                      RESISTOR0603                  0603                   Resistors                                                                                                
R15   1K                       RESISTOR0603                  0603                   Resistors                                                                                                
R16   100K                     RESISTOR0603                  0603                   Resistors                                                                                                
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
